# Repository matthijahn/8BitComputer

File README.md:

# 8BitComputer

This projects aims to build an 8-bit computer for educational purpurses

you will find the files for the seperate componst as KiCad filles as well as simulation data for each component

I want to implement an own machinecode and an asambler

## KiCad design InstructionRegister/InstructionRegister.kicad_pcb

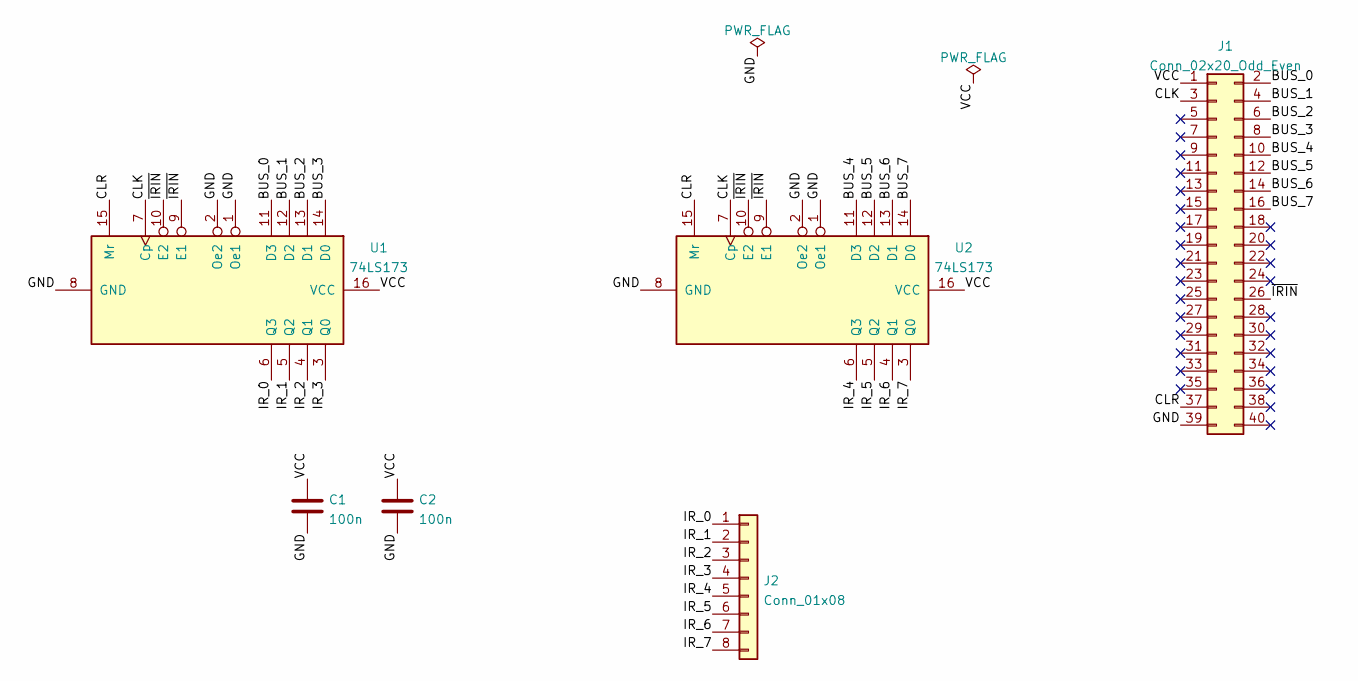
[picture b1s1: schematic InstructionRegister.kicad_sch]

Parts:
C1, C2: 100n; C_Disc_D5.0mm_W2.5mm_P5.00mm
J1: Conn_02x20_Odd_Even; PinSocket_2x20_P2.54mm_Horizontal
J2: Conn_01x08; PinHeader_1x08_P2.54mm_Horizontal
U1, U2: 74LS173; DIP-16_W7.62mm_LongPads

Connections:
/BUS_0: J1.2, U1.11 (D3)
/BUS_1: J1.4, U1.12 (D2)
/BUS_2: J1.6, U1.13 (D1)
/BUS_3: J1.8, U1.14 (D0)
/BUS_4: J1.10, U2.11 (D3)
/BUS_5: J1.12, U2.12 (D2)
/BUS_6: J1.14, U2.13 (D1)
/BUS_7: J1.16, U2.14 (D0)
/CLK: J1.3, U1.7 (Cp), U2.7 (Cp)
/CLR: J1.37, U1.15 (Mr), U2.15 (Mr)
/GND: C1.2, C2.2, J1.39, U1.1 (Oe1), U1.2 (Oe2), U1.8 (GND), U2.1 (Oe1), U2.2 (Oe2), U2.8 (GND)
/IR_0: J2.1, U1.6 (Q3)
/IR_1: J2.2, U1.5 (Q2)
/IR_2: J2.3, U1.4 (Q1)
/IR_3: J2.4, U1.3 (Q0)
/IR_4: J2.5, U2.6 (Q3)
/IR_5: J2.6, U2.5 (Q2)
/IR_6: J2.7, U2.4 (Q1)
/IR_7: J2.8, U2.3 (Q0)
/VCC: C1.1, C2.1, J1.1, U1.16 (VCC), U2.16 (VCC)
/~IRIN: J1.26, U1.9 (E1), U1.10 (E2), U2.9 (E1), U2.10 (E2)

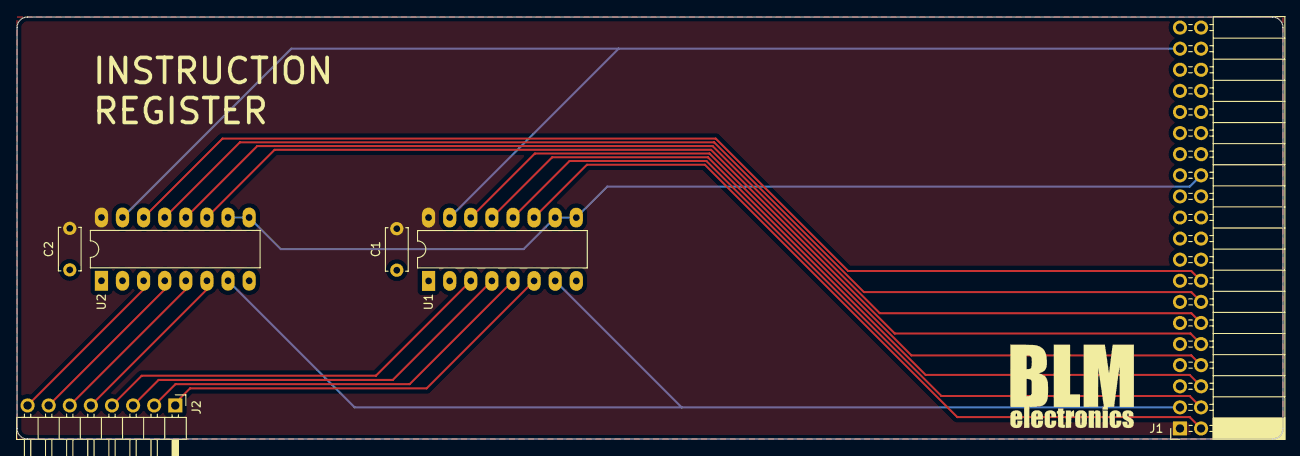
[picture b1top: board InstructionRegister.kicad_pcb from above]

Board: 2 copper layers, 152.4 x 50.8 mm, 6 parts (0 on the bottom side), 21 nets.

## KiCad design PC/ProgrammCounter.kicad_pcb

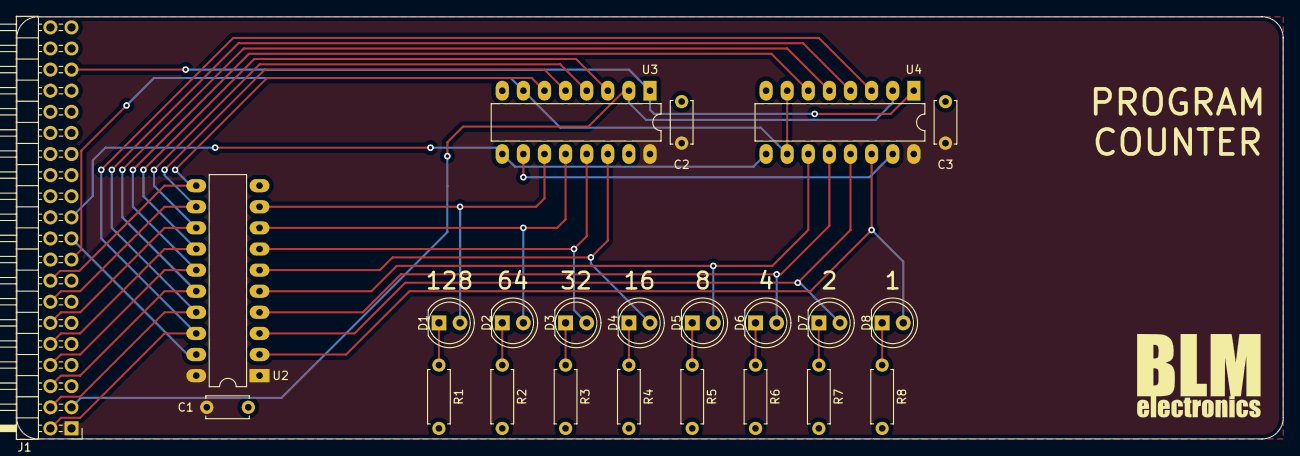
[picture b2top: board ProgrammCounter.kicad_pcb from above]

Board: 2 copper layers, 152.4 x 50.8 mm, 23 parts (0 on the bottom side), 32 nets.

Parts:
C1, C2, C3: 100n; C_Disc_D5.0mm_W2.5mm_P5.00mm
D1, D2, D3, D4, D5, D6, D7, D8: LED; LED_D5.0mm
J1: Conn_02x20_Odd_Even; PinHeader_2x20_P2.54mm_Horizontal
R1, R2, R3, R4, R5, R6, R7, R8: R; R_Axial_DIN0207_L6.3mm_D2.5mm_P7.62mm_Horizontal
U2: 74HC245; DIP-20_W7.62mm_LongPads
U3, U4: 74LS161; DIP-16_W7.62mm_LongPads

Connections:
/BUS_0: J1.2, U2.18, U4.3
/BUS_1: J1.4, U2.17, U4.4
/BUS_2: J1.6, U2.16, U4.5
/BUS_3: J1.8, U2.15, U4.6
/BUS_4: J1.10, U2.14, U3.3
/BUS_5: J1.12, U2.13, U3.4
/BUS_6: J1.14, U2.12, U3.5
/BUS_7: J1.16, U2.11, U3.6
/CLK: J1.3, U3.2, U4.2
/GND: C1.2, C2.2, C3.2, J1.39, R1.2, R2.2, R3.2, R4.2, R5.2, R6.2, R7.2, R8.2, U2.10, U3.8, U4.8
/PCUP: J1.17, U3.7, U4.7, U4.10
/VCC: C1.1, C2.1, C3.1, J1.1, U2.1, U2.20, U3.16, U4.16
/~CLR: J1.35, U3.1, U4.1
/~PCIN: J1.21, U3.9, U4.9
/~PCOUT: J1.19, U2.19
unnamed: D1.1, R1.1
unnamed: D1.2, U2.9, U3.11
unnamed: D2.1, R2.1
unnamed: D2.2, U2.8, U3.12
unnamed: D3.1, R3.1
unnamed: D3.2, U2.7, U3.13
unnamed: D4.1, R4.1
unnamed: D4.2, U2.6, U3.14
unnamed: D5.1, R5.1
unnamed: D5.2, U2.5, U4.11
unnamed: D6.1, R6.1
unnamed: D6.2, U2.4, U4.12
unnamed: D7.1, R7.1
unnamed: D7.2, U2.3, U4.13
unnamed: D8.1, R8.1
unnamed: D8.2, U2.2, U4.14
unnamed: U3.10, U4.15

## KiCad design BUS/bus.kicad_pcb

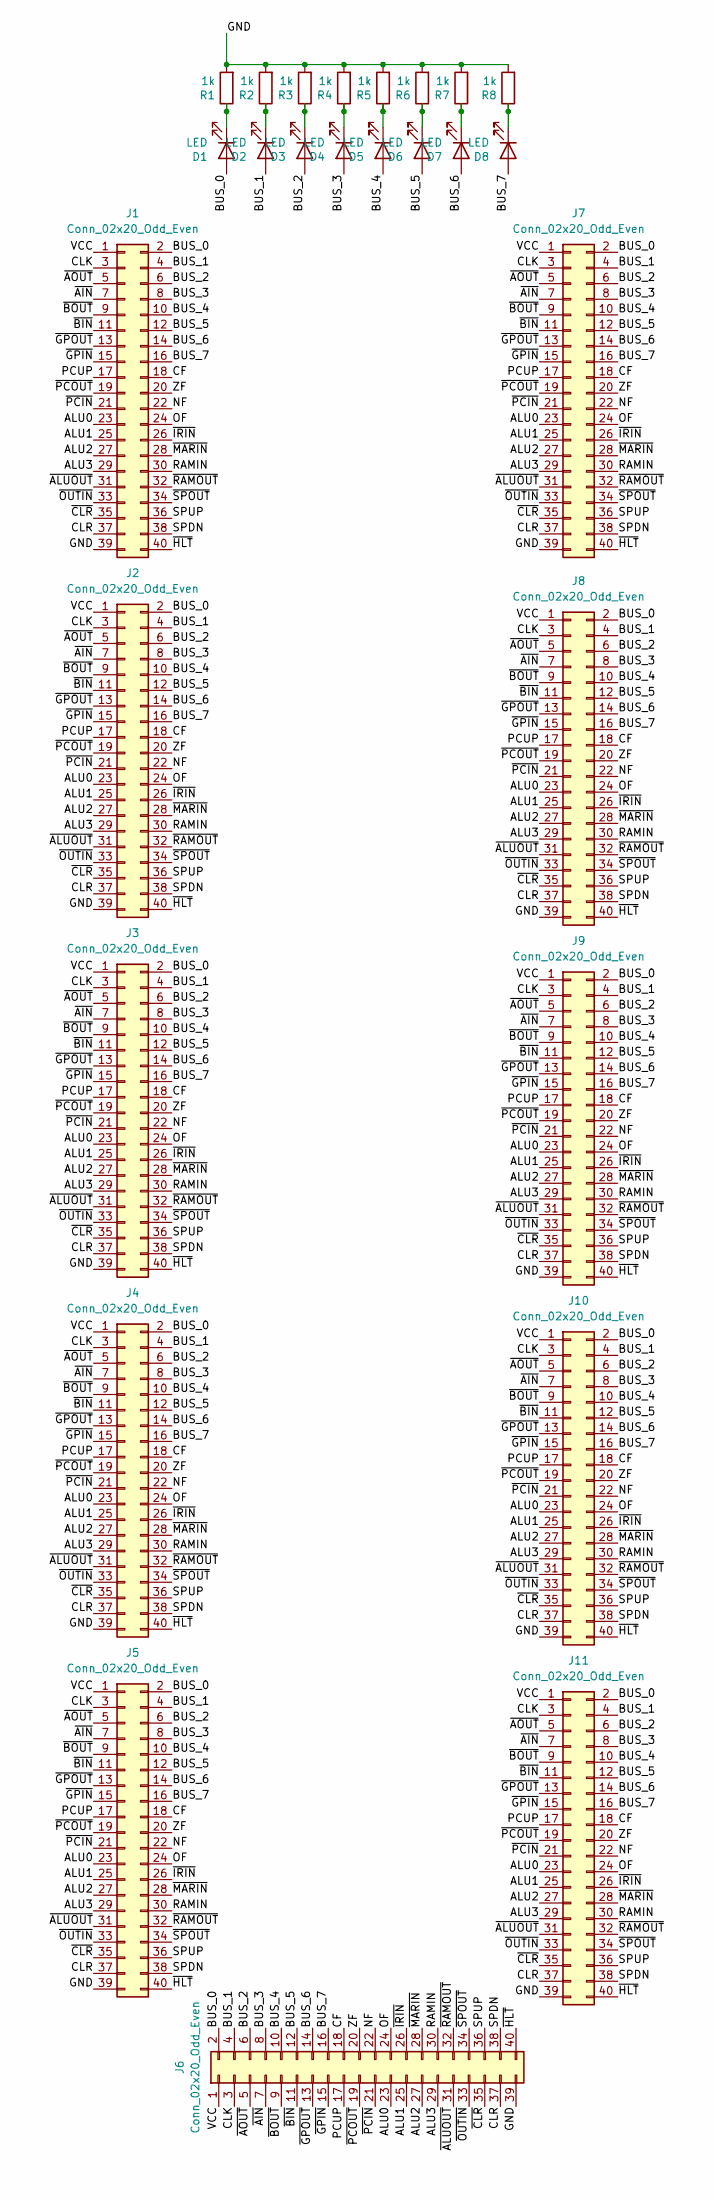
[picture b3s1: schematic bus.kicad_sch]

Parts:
D1, D2, D3, D4, D5, D6, D7, D8: LED; LED_D5.0mm
J1, J2, J3, J4, J5, J6: Conn_02x20_Odd_Even; PinHeader_2x20_P2.54mm_Horizontal
J7, J8, J9, J10, J11: Conn_02x20_Odd_Even; PinSocket_2x20_P2.54mm_Horizontal
R1, R2, R3, R4, R5, R6, R7, R8: 1k; R_Axial_DIN0207_L6.3mm_D2.5mm_P7.62mm_Horizontal

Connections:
/ALU0: J1.23, J2.23, J3.23, J4.23, J5.23, J6.23, J7.23, J8.23, J9.23, J10.23, J11.23
/ALU1: J1.25, J2.25, J3.25, J4.25, J5.25, J6.25, J7.25, J8.25, J9.25, J10.25, J11.25
/ALU2: J1.27, J2.27, J3.27, J4.27, J5.27, J6.27, J7.27, J8.27, J9.27, J10.27, J11.27
/ALU3: J1.29, J2.29, J3.29, J4.29, J5.29, J6.29, J7.29, J8.29, J9.29, J10.29, J11.29
/BUS_0: D1.2 (A), J1.2, J2.2, J3.2, J4.2, J5.2, J6.2, J7.2, J8.2, J9.2, J10.2, J11.2
/BUS_1: D2.2 (A), J1.4, J2.4, J3.4, J4.4, J5.4, J6.4, J7.4, J8.4, J9.4, J10.4, J11.4
/BUS_2: D3.2 (A), J1.6, J2.6, J3.6, J4.6, J5.6, J6.6, J7.6, J8.6, J9.6, J10.6, J11.6
/BUS_3: D4.2 (A), J1.8, J2.8, J3.8, J4.8, J5.8, J6.8, J7.8, J8.8, J9.8, J10.8, J11.8
/BUS_4: D5.2 (A), J1.10, J2.10, J3.10, J4.10, J5.10, J6.10, J7.10, J8.10, J9.10, J10.10, J11.10
/BUS_5: D6.2 (A), J1.12, J2.12, J3.12, J4.12, J5.12, J6.12, J7.12, J8.12, J9.12, J10.12, J11.12
/BUS_6: D7.2 (A), J1.14, J2.14, J3.14, J4.14, J5.14, J6.14, J7.14, J8.14, J9.14, J10.14, J11.14
/BUS_7: D8.2 (A), J1.16, J2.16, J3.16, J4.16, J5.16, J6.16, J7.16, J8.16, J9.16, J10.16, J11.16
/CF: J1.18, J2.18, J3.18, J4.18, J5.18, J6.18, J7.18, J8.18, J9.18, J10.18, J11.18
/CLK: J1.3, J2.3, J3.3, J4.3, J5.3, J6.3, J7.3, J8.3, J9.3, J10.3, J11.3
/CLR: J1.37, J2.37, J3.37, J4.37, J5.37, J6.37, J7.37, J8.37, J9.37, J10.37, J11.37
/GND: J1.39, J2.39, J3.39, J4.39, J5.39, J6.39, J7.39, J8.39, J9.39, J10.39, J11.39, R1.2, R2.2, R3.2, R4.2, R5.2, R6.2, R7.2, R8.2
/NF: J1.22, J2.22, J3.22, J4.22, J5.22, J6.22, J7.22, J8.22, J9.22, J10.22, J11.22
/OF: J1.24, J2.24, J3.24, J4.24, J5.24, J6.24, J7.24, J8.24, J9.24, J10.24, J11.24
/PCUP: J1.17, J2.17, J3.17, J4.17, J5.17, J6.17, J7.17, J8.17, J9.17, J10.17, J11.17
/RAMIN: J1.30, J2.30, J3.30, J4.30, J5.30, J6.30, J7.30, J8.30, J9.30, J10.30, J11.30
/SPDN: J1.38, J2.38, J3.38, J4.38, J5.38, J6.38, J7.38, J8.38, J9.38, J10.38, J11.38
/SPUP: J1.36, J2.36, J3.36, J4.36, J5.36, J6.36, J7.36, J8.36, J9.36, J10.36, J11.36
/VCC: J1.1, J2.1, J3.1, J4.1, J5.1, J6.1, J7.1, J8.1, J9.1, J10.1, J11.1
/ZF: J1.20, J2.20, J3.20, J4.20, J5.20, J6.20, J7.20, J8.20, J9.20, J10.20, J11.20
/~AIN: J1.7, J2.7, J3.7, J4.7, J5.7, J6.7, J7.7, J8.7, J9.7, J10.7, J11.7
/~ALUOUT: J1.31, J2.31, J3.31, J4.31, J5.31, J6.31, J7.31, J8.31, J9.31, J10.31, J11.31
/~AOUT: J1.5, J2.5, J3.5, J4.5, J5.5, J6.5, J7.5, J8.5, J9.5, J10.5, J11.5
/~BIN: J1.11, J2.11, J3.11, J4.11, J5.11, J6.11, J7.11, J8.11, J9.11, J10.11, J11.11
/~BOUT: J1.9, J2.9, J3.9, J4.9, J5.9, J6.9, J7.9, J8.9, J9.9, J10.9, J11.9
/~CLR: J1.35, J2.35, J3.35, J4.35, J5.35, J6.35, J7.35, J8.35, J9.35, J10.35, J11.35
/~GPIN: J1.15, J2.15, J3.15, J4.15, J5.15, J6.15, J7.15, J8.15, J9.15, J10.15, J11.15
/~GPOUT: J1.13, J2.13, J3.13, J4.13, J5.13, J6.13, J7.13, J8.13, J9.13, J10.13, J11.13
/~HLT: J1.40, J2.40, J3.40, J4.40, J5.40, J6.40, J7.40, J8.40, J9.40, J10.40, J11.40
/~IRIN: J1.26, J2.26, J3.26, J4.26, J5.26, J6.26, J7.26, J8.26, J9.26, J10.26, J11.26
/~MARIN: J1.28, J2.28, J3.28, J4.28, J5.28, J6.28, J7.28, J8.28, J9.28, J10.28, J11.28
/~OUTIN: J1.33, J2.33, J3.33, J4.33, J5.33, J6.33, J7.33, J8.33, J9.33, J10.33, J11.33
/~PCIN: J1.21, J2.21, J3.21, J4.21, J5.21, J6.21, J7.21, J8.21, J9.21, J10.21, J11.21
/~PCOUT: J1.19, J2.19, J3.19, J4.19, J5.19, J6.19, J7.19, J8.19, J9.19, J10.19, J11.19
/~RAMOUT: J1.32, J2.32, J3.32, J4.32, J5.32, J6.32, J7.32, J8.32, J9.32, J10.32, J11.32
/~SPOUT: J1.34, J2.34, J3.34, J4.34, J5.34, J6.34, J7.34, J8.34, J9.34, J10.34, J11.34
unnamed: D1.1 (K), R1.1
unnamed: D2.1 (K), R2.1
unnamed: D3.1 (K), R3.1
unnamed: D4.1 (K), R4.1
unnamed: D5.1 (K), R5.1
unnamed: D6.1 (K), R6.1
unnamed: D7.1 (K), R7.1
unnamed: D8.1 (K), R8.1

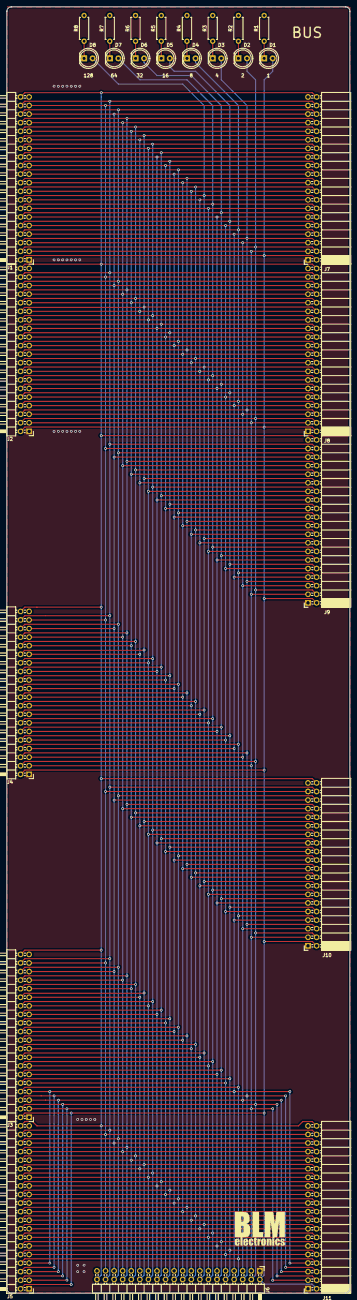
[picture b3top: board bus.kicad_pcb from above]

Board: 2 copper layers, 101.6 x 381.0 mm, 27 parts (0 on the bottom side), 48 nets.

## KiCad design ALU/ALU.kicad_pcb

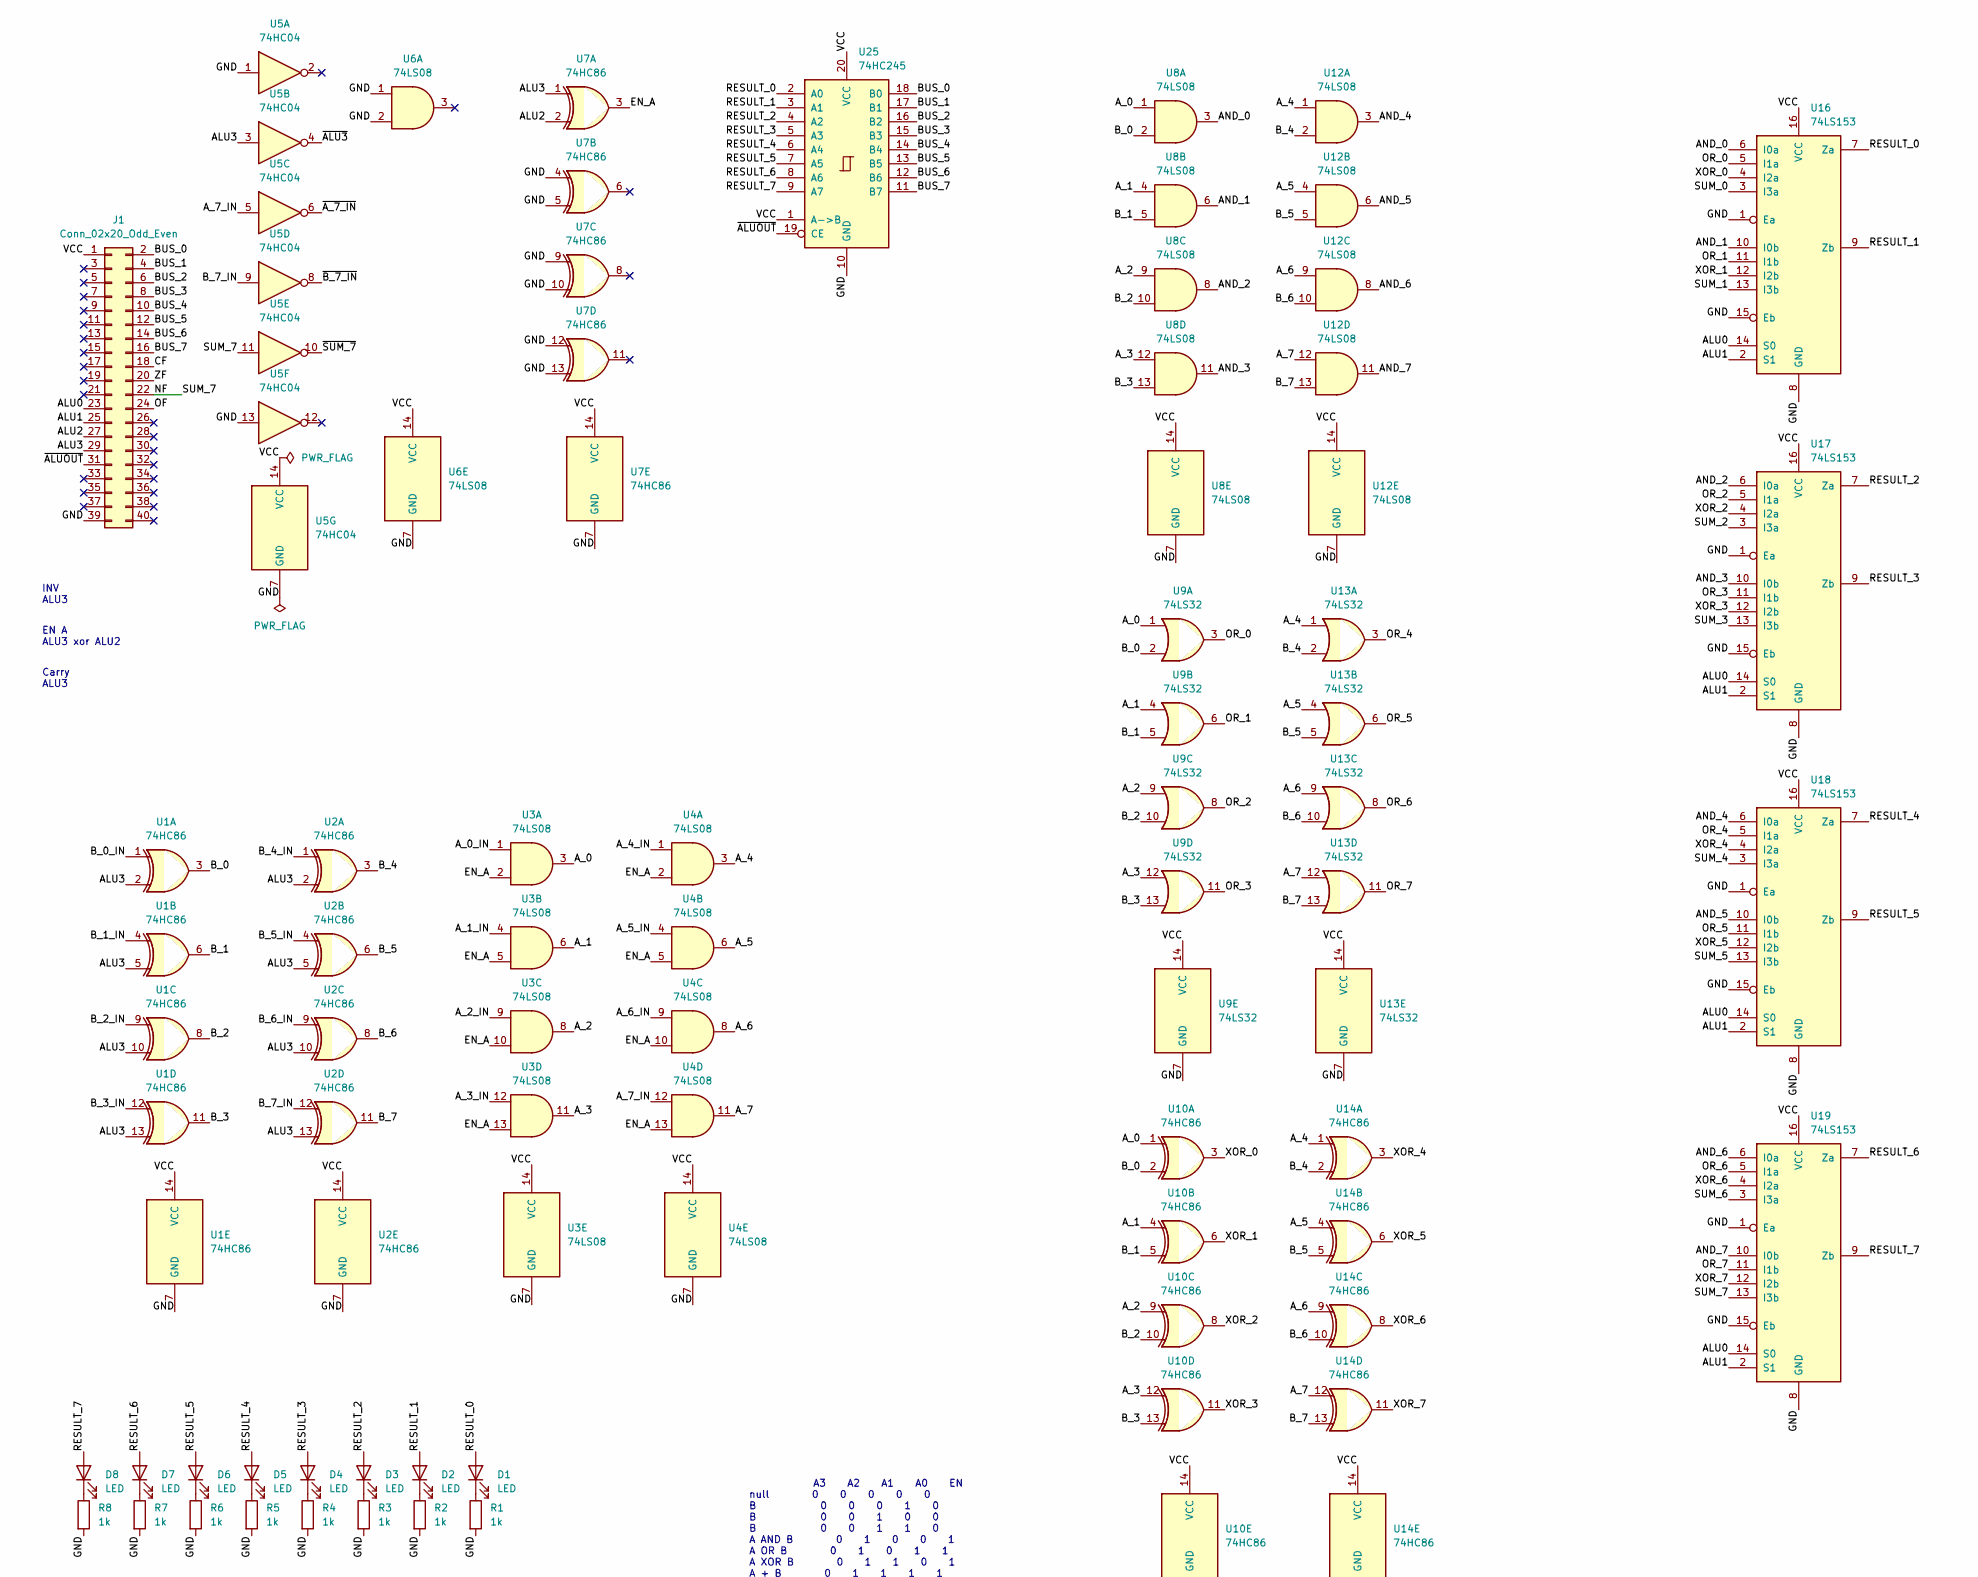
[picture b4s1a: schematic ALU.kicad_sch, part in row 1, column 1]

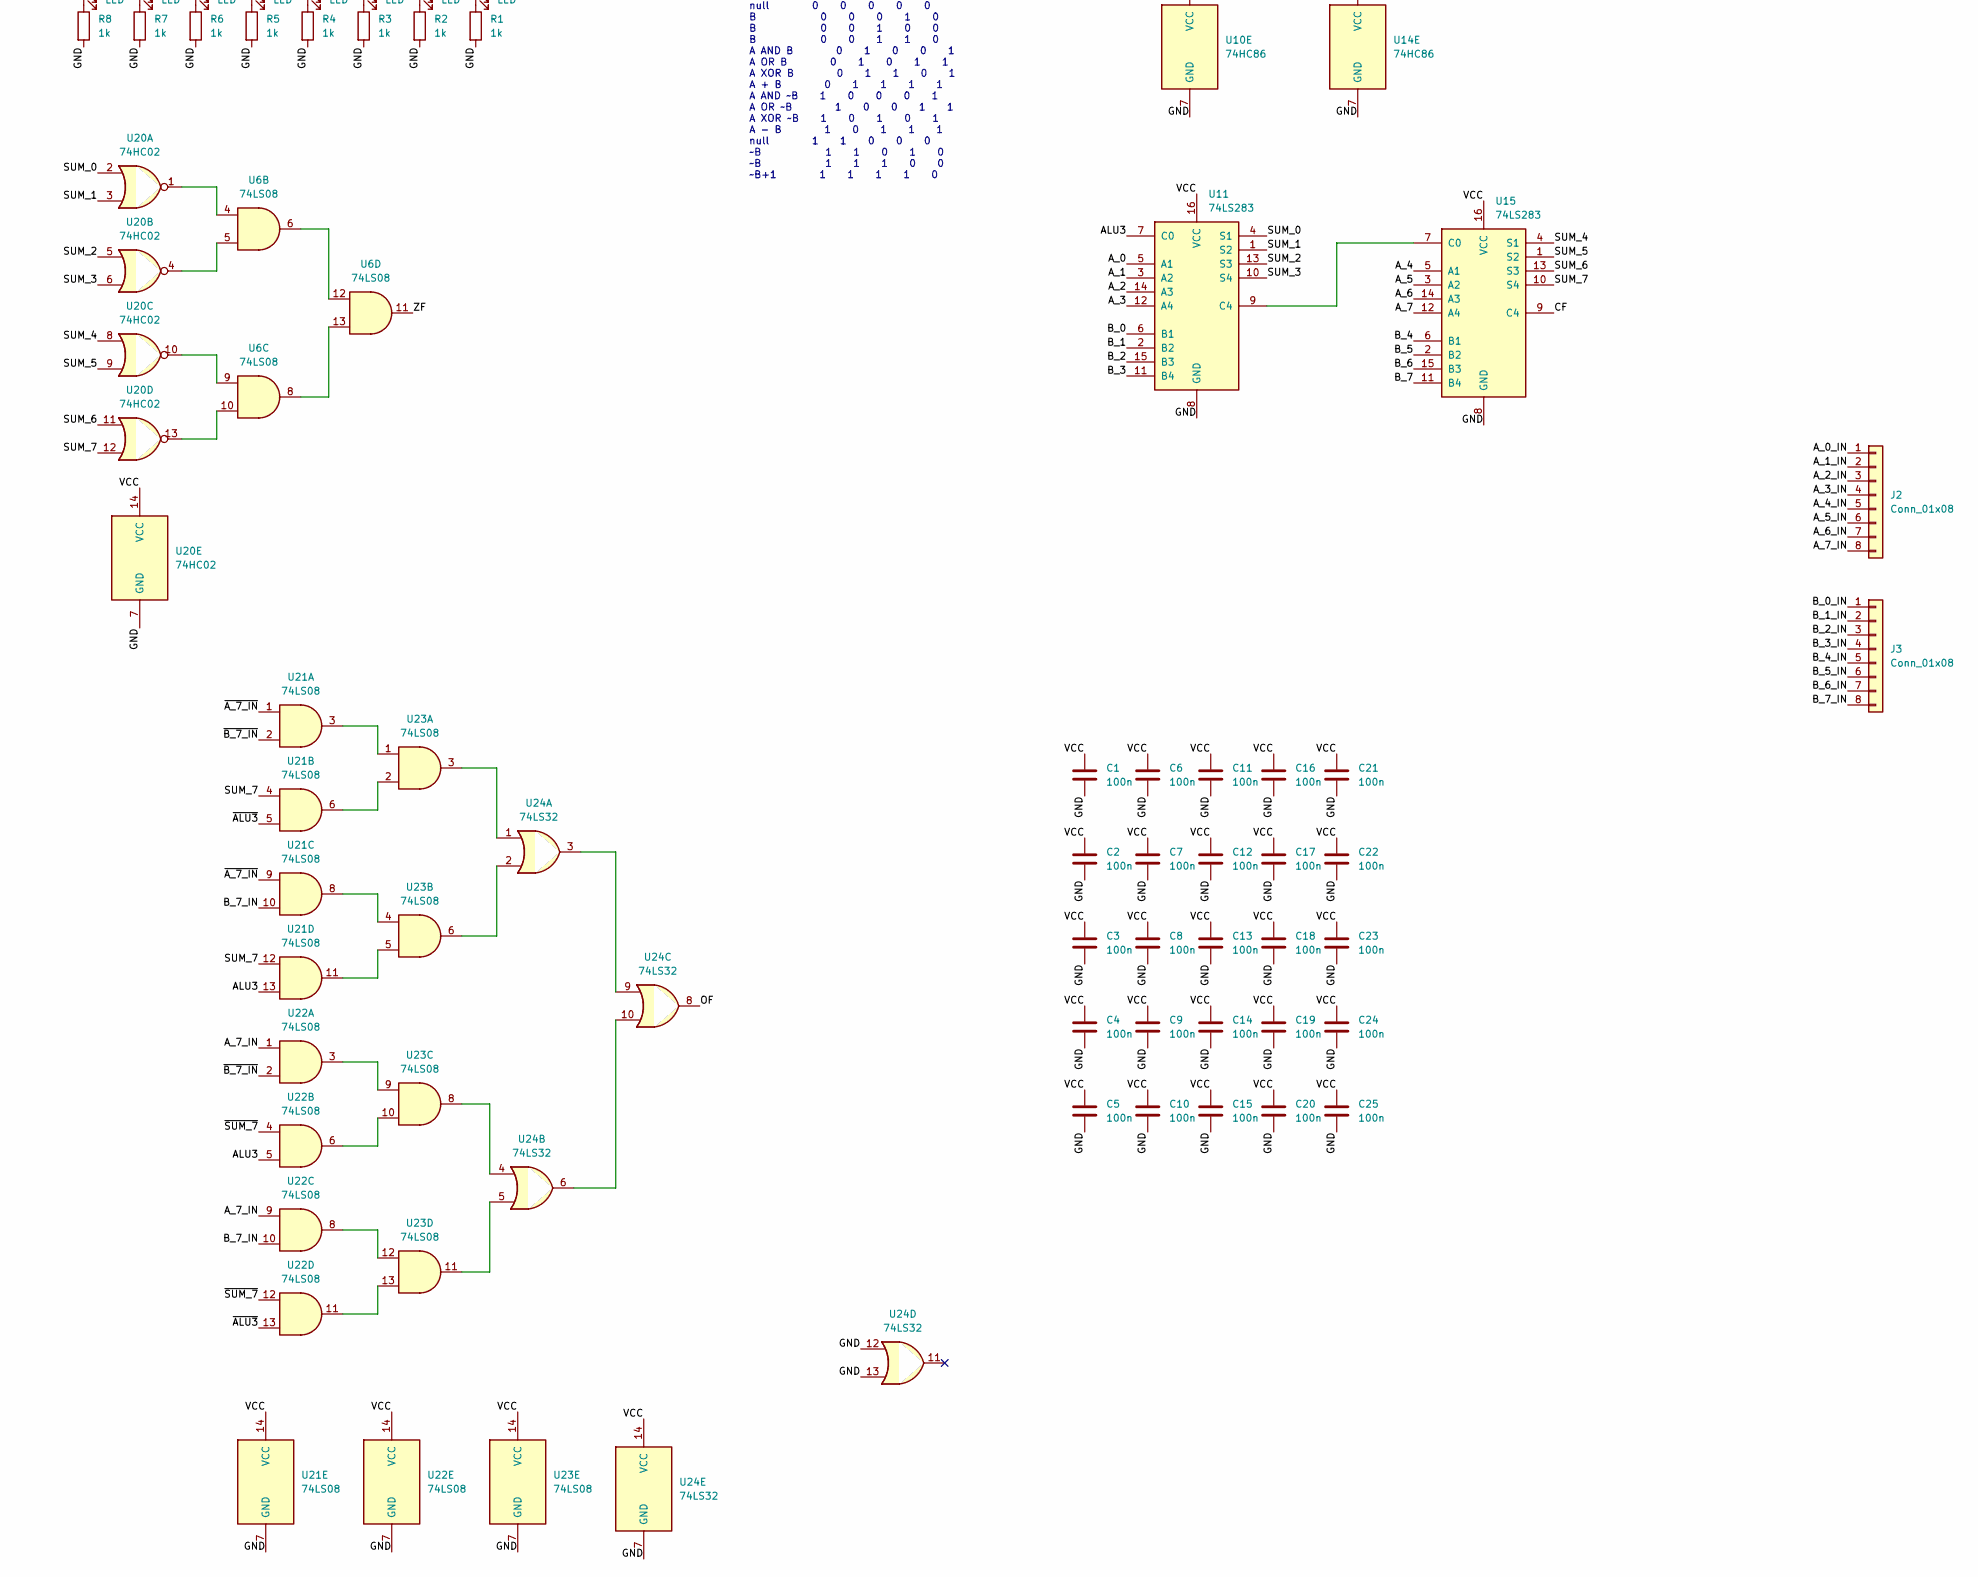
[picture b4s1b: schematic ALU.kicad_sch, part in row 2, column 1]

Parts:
C1, C2, C3, C4, C5, C6, C7, C8, C9, C10, C11, C12, C13, C14, C15, C16, C17, C18, C19, C20, C21, C22, C23, C24, C25: 100n; C_Disc_D5.0mm_W2.5mm_P5.00mm
D1, D2, D3, D4, D5, D6, D7, D8: LED; LED_D5.0mm
J1: Conn_02x20_Odd_Even; PinHeader_2x20_P2.54mm_Horizontal
J2, J3: Conn_01x08; PinSocket_1x08_P2.54mm_Horizontal
R1, R2, R3, R4, R5, R6, R7, R8: 1k; R_Axial_DIN0207_L6.3mm_D2.5mm_P7.62mm_Horizontal
U1, U2, U7, U10, U14: 74HC86; DIP-14_W7.62mm_LongPads
U3, U4, U6, U8, U12, U21, U22, U23: 74LS08; DIP-14_W7.62mm_LongPads
U5: 74HC04; DIP-14_W7.62mm_LongPads
U9, U13, U24: 74LS32; DIP-14_W7.62mm_LongPads
U11, U15: 74LS283; DIP-16_W7.62mm_LongPads
U16, U17, U18, U19: 74LS153; DIP-16_W7.62mm_LongPads
U20: 74HC02; DIP-14_W7.62mm_LongPads
U25: 74HC245; DIP-20_W7.62mm_LongPads

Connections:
/ALU0: J1.23, U16.14 (S0), U17.14 (S0), U18.14 (S0), U19.14 (S0)
/ALU1: J1.25, U16.2 (S1), U17.2 (S1), U18.2 (S1), U19.2 (S1)
/ALU2: J1.27, U7.2
/ALU3: J1.29, U1.2, U1.5, U1.10, U1.13, U2.2, U2.5, U2.10, U2.13, U5.3, U7.1, U11.7 (C0), U21.13, U22.5
/AND_0: U8.3, U16.6 (I0a)
/AND_1: U8.6, U16.10 (I0b)
/AND_2: U8.8, U17.6 (I0a)
/AND_3: U8.11, U17.10 (I0b)
/AND_4: U12.3, U18.6 (I0a)
/AND_5: U12.6, U18.10 (I0b)
/AND_6: U12.8, U19.6 (I0a)
/AND_7: U12.11, U19.10 (I0b)
/A_0: U3.3, U8.1, U9.1, U10.1, U11.5 (A1)
/A_0_IN: J2.1, U3.1
/A_1: U3.6, U8.4, U9.4, U10.4, U11.3 (A2)
/A_1_IN: J2.2, U3.4
/A_2: U3.8, U8.9, U9.9, U10.9, U11.14 (A3)
/A_2_IN: J2.3, U3.9
/A_3: U3.11, U8.12, U9.12, U10.12, U11.12 (A4)
/A_3_IN: J2.4, U3.12
/A_4: U4.3, U12.1, U13.1, U14.1, U15.5 (A1)
/A_4_IN: J2.5, U4.1
/A_5: U4.6, U12.4, U13.4, U14.4, U15.3 (A2)
/A_5_IN: J2.6, U4.4
/A_6: U4.8, U12.9, U13.9, U14.9, U15.14 (A3)
/A_6_IN: J2.7, U4.9
/A_7: U4.11, U12.12, U13.12, U14.12, U15.12 (A4)
/A_7_IN: J2.8, U4.12, U5.5, U22.1, U22.9
/BUS_0: J1.2, U25.18 (B0)
/BUS_1: J1.4, U25.17 (B1)
/BUS_2: J1.6, U25.16 (B2)
/BUS_3: J1.8, U25.15 (B3)
/BUS_4: J1.10, U25.14 (B4)
/BUS_5: J1.12, U25.13 (B5)
/BUS_6: J1.14, U25.12 (B6)
/BUS_7: J1.16, U25.11 (B7)
/B_0: U1.3, U8.2, U9.2, U10.2, U11.6 (B1)
/B_0_IN: J3.1, U1.1
/B_1: U1.6, U8.5, U9.5, U10.5, U11.2 (B2)
/B_1_IN: J3.2, U1.4
/B_2: U1.8, U8.10, U9.10, U10.10, U11.15 (B3)
/B_2_IN: J3.3, U1.9
/B_3: U1.11, U8.13, U9.13, U10.13, U11.11 (B4)
/B_3_IN: J3.4, U1.12
/B_4: U2.3, U12.2, U13.2, U14.2, U15.6 (B1)
/B_4_IN: J3.5, U2.1
/B_5: U2.6, U12.5, U13.5, U14.5, U15.2 (B2)
/B_5_IN: J3.6, U2.4
/B_6: U2.8, U12.10, U13.10, U14.10, U15.15 (B3)
/B_6_IN: J3.7, U2.9
/B_7: U2.11, U12.13, U13.13, U14.13, U15.11 (B4)
/B_7_IN: J3.8, U2.12, U5.9, U21.10, U22.10
/CF: J1.18, U15.9 (C4)
/EN_A: U3.2, U3.5, U3.10, U3.13, U4.2, U4.5, U4.10, U4.13, U7.3
/GND: C1.2, C2.2, C3.2, C4.2, C5.2, C6.2, C7.2, C8.2, C9.2, C10.2, C11.2, C12.2, C13.2, C14.2, C15.2, C16.2, C17.2, C18.2, C19.2, C20.2, C21.2, C22.2, C23.2, C24.2, C25.2, J1.39, R1.2, R2.2, R3.2, R4.2, R5.2, R6.2, R7.2, R8.2, U1.7 (GND), U2.7 (GND), U3.7 (GND), U4.7 (GND), U5.1, U5.7 (GND), U5.13, U6.1, U6.2, U6.7 (GND), U7.4, U7.5, U7.7 (GND), U7.9, U7.10, U7.12, U7.13, U8.7 (GND), U9.7 (GND), U10.7 (GND), U11.8 (GND), U12.7 (GND), U13.7 (GND), U14.7 (GND), U15.8 (GND), U16.1 (Ea), U16.8 (GND), U16.15 (Eb), U17.1 (Ea), U17.8 (GND), U17.15 (Eb), U18.1 (Ea), U18.8 (GND), U18.15 (Eb), U19.1 (Ea), U19.8 (GND), U19.15 (Eb), U20.7 (GND), U21.7 (GND), U22.7 (GND), U23.7 (GND), U24.7 (GND), U24.12, U24.13, U25.10 (GND)
/NF: J1.22, U5.11, U15.10 (S4), U19.13 (I3b), U20.12, U21.4, U21.12
/OF: J1.24, U24.8
/OR_0: U9.3, U16.5 (I1a)
/OR_1: U9.6, U16.11 (I1b)
/OR_2: U9.8, U17.5 (I1a)
/OR_3: U9.11, U17.11 (I1b)
/OR_4: U13.3, U18.5 (I1a)
/OR_5: U13.6, U18.11 (I1b)
/OR_6: U13.8, U19.5 (I1a)
/OR_7: U13.11, U19.11 (I1b)
/RESULT_0: D1.2 (A), U16.7 (Za), U25.2 (A0)
/RESULT_1: D2.2 (A), U16.9 (Zb), U25.3 (A1)
/RESULT_2: D3.2 (A), U17.7 (Za), U25.4 (A2)
/RESULT_3: D4.2 (A), U17.9 (Zb), U25.5 (A3)
/RESULT_4: D5.2 (A), U18.7 (Za), U25.6 (A4)
/RESULT_5: D6.2 (A), U18.9 (Zb), U25.7 (A5)
/RESULT_6: D7.2 (A), U19.7 (Za), U25.8 (A6)
/RESULT_7: D8.2 (A), U19.9 (Zb), U25.9 (A7)
/SUM_0: U11.4 (S1), U16.3 (I3a), U20.2
/SUM_1: U11.1 (S2), U16.13 (I3b), U20.3
/SUM_2: U11.13 (S3), U17.3 (I3a), U20.5
/SUM_3: U11.10 (S4), U17.13 (I3b), U20.6
/SUM_4: U15.4 (S1), U18.3 (I3a), U20.8
/SUM_5: U15.1 (S2), U18.13 (I3b), U20.9
/SUM_6: U15.13 (S3), U19.3 (I3a), U20.11
/VCC: C1.1, C2.1, C3.1, C4.1, C5.1, C6.1, C7.1, C8.1, C9.1, C10.1, C11.1, C12.1, C13.1, C14.1, C15.1, C16.1, C17.1, C18.1, C19.1, C20.1, C21.1, C22.1, C23.1, C24.1, C25.1, J1.1, U1.14 (VCC), U2.14 (VCC), U3.14 (VCC), U4.14 (VCC), U5.14 (VCC), U6.14 (VCC), U7.14 (VCC), U8.14 (VCC), U9.14 (VCC), U10.14 (VCC), U11.16 (VCC), U12.14 (VCC), U13.14 (VCC), U14.14 (VCC), U15.16 (VCC), U16.16 (VCC), U17.16 (VCC), U18.16 (VCC), U19.16 (VCC), U20.14 (VCC), U21.14 (VCC), U22.14 (VCC), U23.14 (VCC), U24.14 (VCC), U25.1 (A->B), U25.20 (VCC)
/XOR_0: U10.3, U16.4 (I2a)
/XOR_1: U10.6, U16.12 (I2b)
/XOR_2: U10.8, U17.4 (I2a)
/XOR_3: U10.11, U17.12 (I2b)
/XOR_4: U14.3, U18.4 (I2a)
/XOR_5: U14.6, U18.12 (I2b)
/XOR_6: U14.8, U19.4 (I2a)
/XOR_7: U14.11, U19.12 (I2b)
/ZF: J1.20, U6.11
/~ALU3: U5.4, U21.5, U22.13
/~ALUOUT: J1.31, U25.19 (CE)
/~A_7_IN: U5.6, U21.1, U21.9
/~B_7_IN: U5.8, U21.2, U22.2
/~SUM_7: U5.10, U22.4, U22.12
unnamed: D1.1 (K), R1.1
unnamed: D2.1 (K), R2.1
unnamed: D3.1 (K), R3.1
unnamed: D4.1 (K), R4.1
unnamed: D5.1 (K), R5.1
unnamed: D6.1 (K), R6.1
unnamed: D7.1 (K), R7.1
unnamed: D8.1 (K), R8.1
unnamed: U6.6, U6.12
unnamed: U6.8, U6.13
unnamed: U11.9 (C4), U15.7 (C0)
unnamed: U6.4, U20.1
unnamed: U6.5, U20.4
unnamed: U6.9, U20.10
unnamed: U6.10, U20.13
unnamed: U21.3, U23.1
unnamed: U21.6, U23.2
unnamed: U21.8, U23.4
unnamed: U21.11, U23.5
unnamed: U22.3, U23.9
unnamed: U22.6, U23.10
unnamed: U22.8, U23.12
unnamed: U22.11, U23.13
unnamed: U23.3, U24.1
unnamed: U23.6, U24.2
unnamed: U23.8, U24.4
unnamed: U23.11, U24.5
unnamed: U24.3, U24.9
unnamed: U24.6, U24.10

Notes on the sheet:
Carry ALU3
EN A ALU3 xor ALU2
INV ALU3
A3 A2 A1 A0 EN null 0 0 0 0 0 B 0 0 0 1 0 B 0 0 1 0 0 B 0 0 1 1 0 A AND B 0 1 0 0 1 A OR B 0 1 0 1 1 A XOR B 0 1 1 0 1 A + B 0 1 1 1 1 A AND ~B 1 0 0 0 1 A OR ~B 1 0 0 1 1 A XOR ~B 1 0 1 0 1 A - B 1 0 1 1 1 null 1 1 0 0 0 ~B 1 1 0 1 0 ~B 1 1 1 0 0 ~B+1 1 1 1 1 0

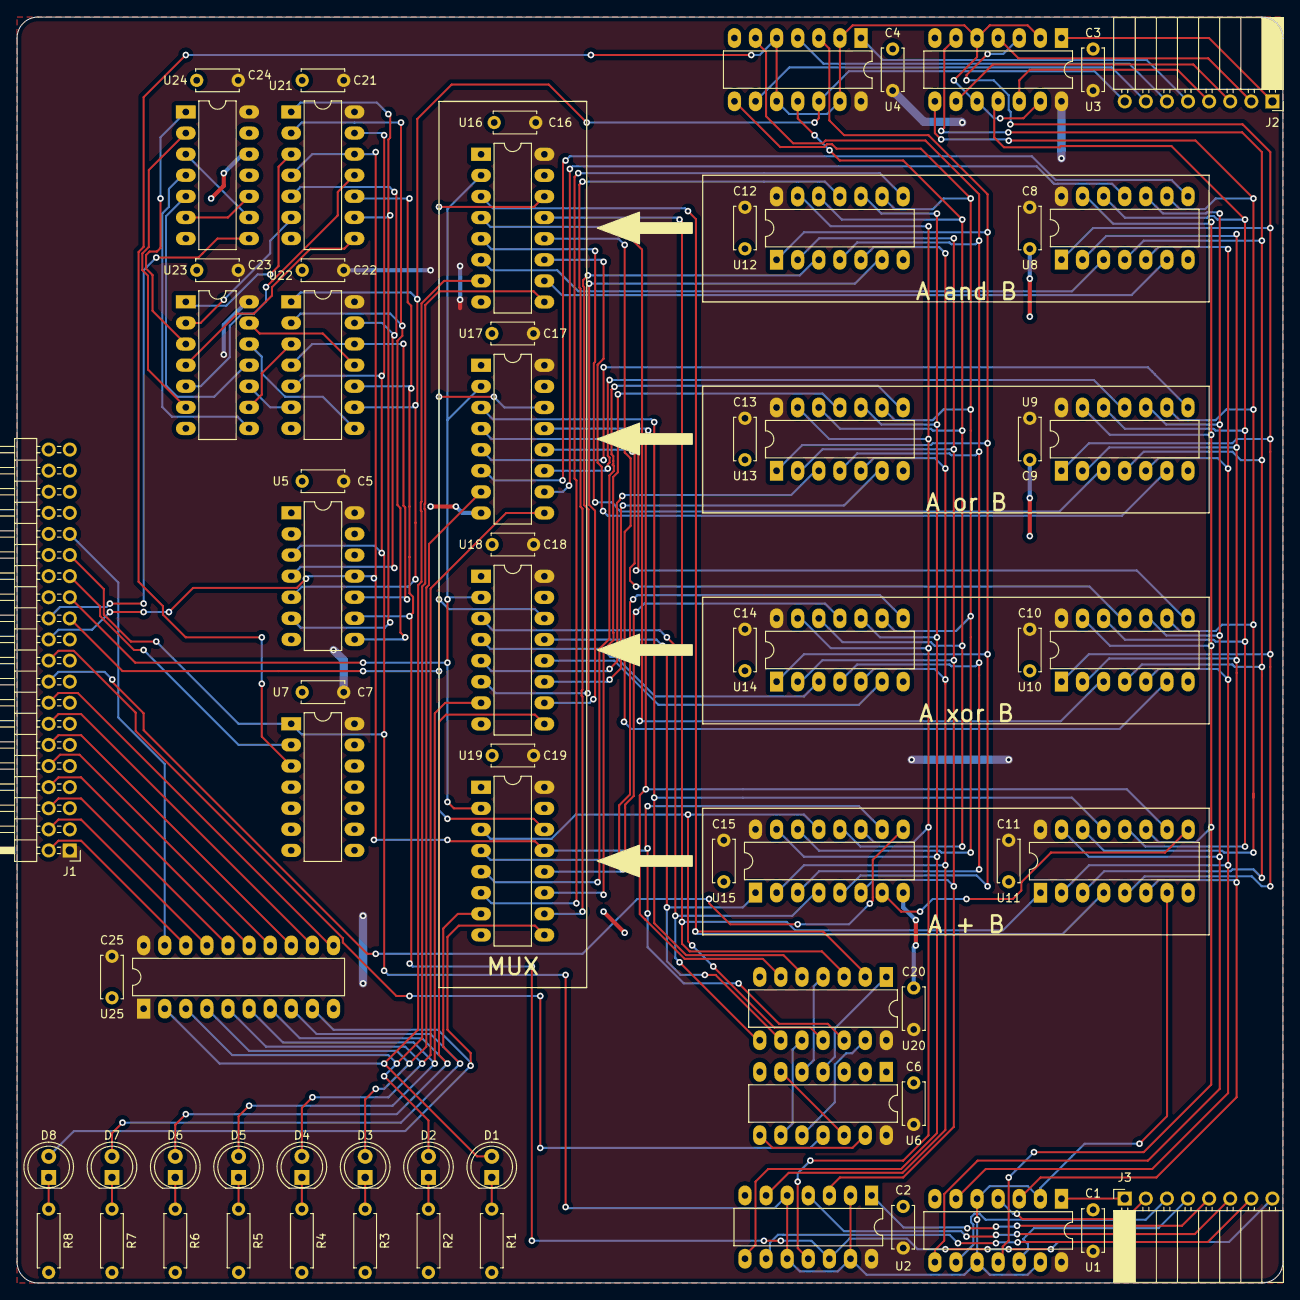
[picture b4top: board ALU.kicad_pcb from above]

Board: 2 copper layers, 152.4 x 152.4 mm, 69 parts (0 on the bottom side), 124 nets.
